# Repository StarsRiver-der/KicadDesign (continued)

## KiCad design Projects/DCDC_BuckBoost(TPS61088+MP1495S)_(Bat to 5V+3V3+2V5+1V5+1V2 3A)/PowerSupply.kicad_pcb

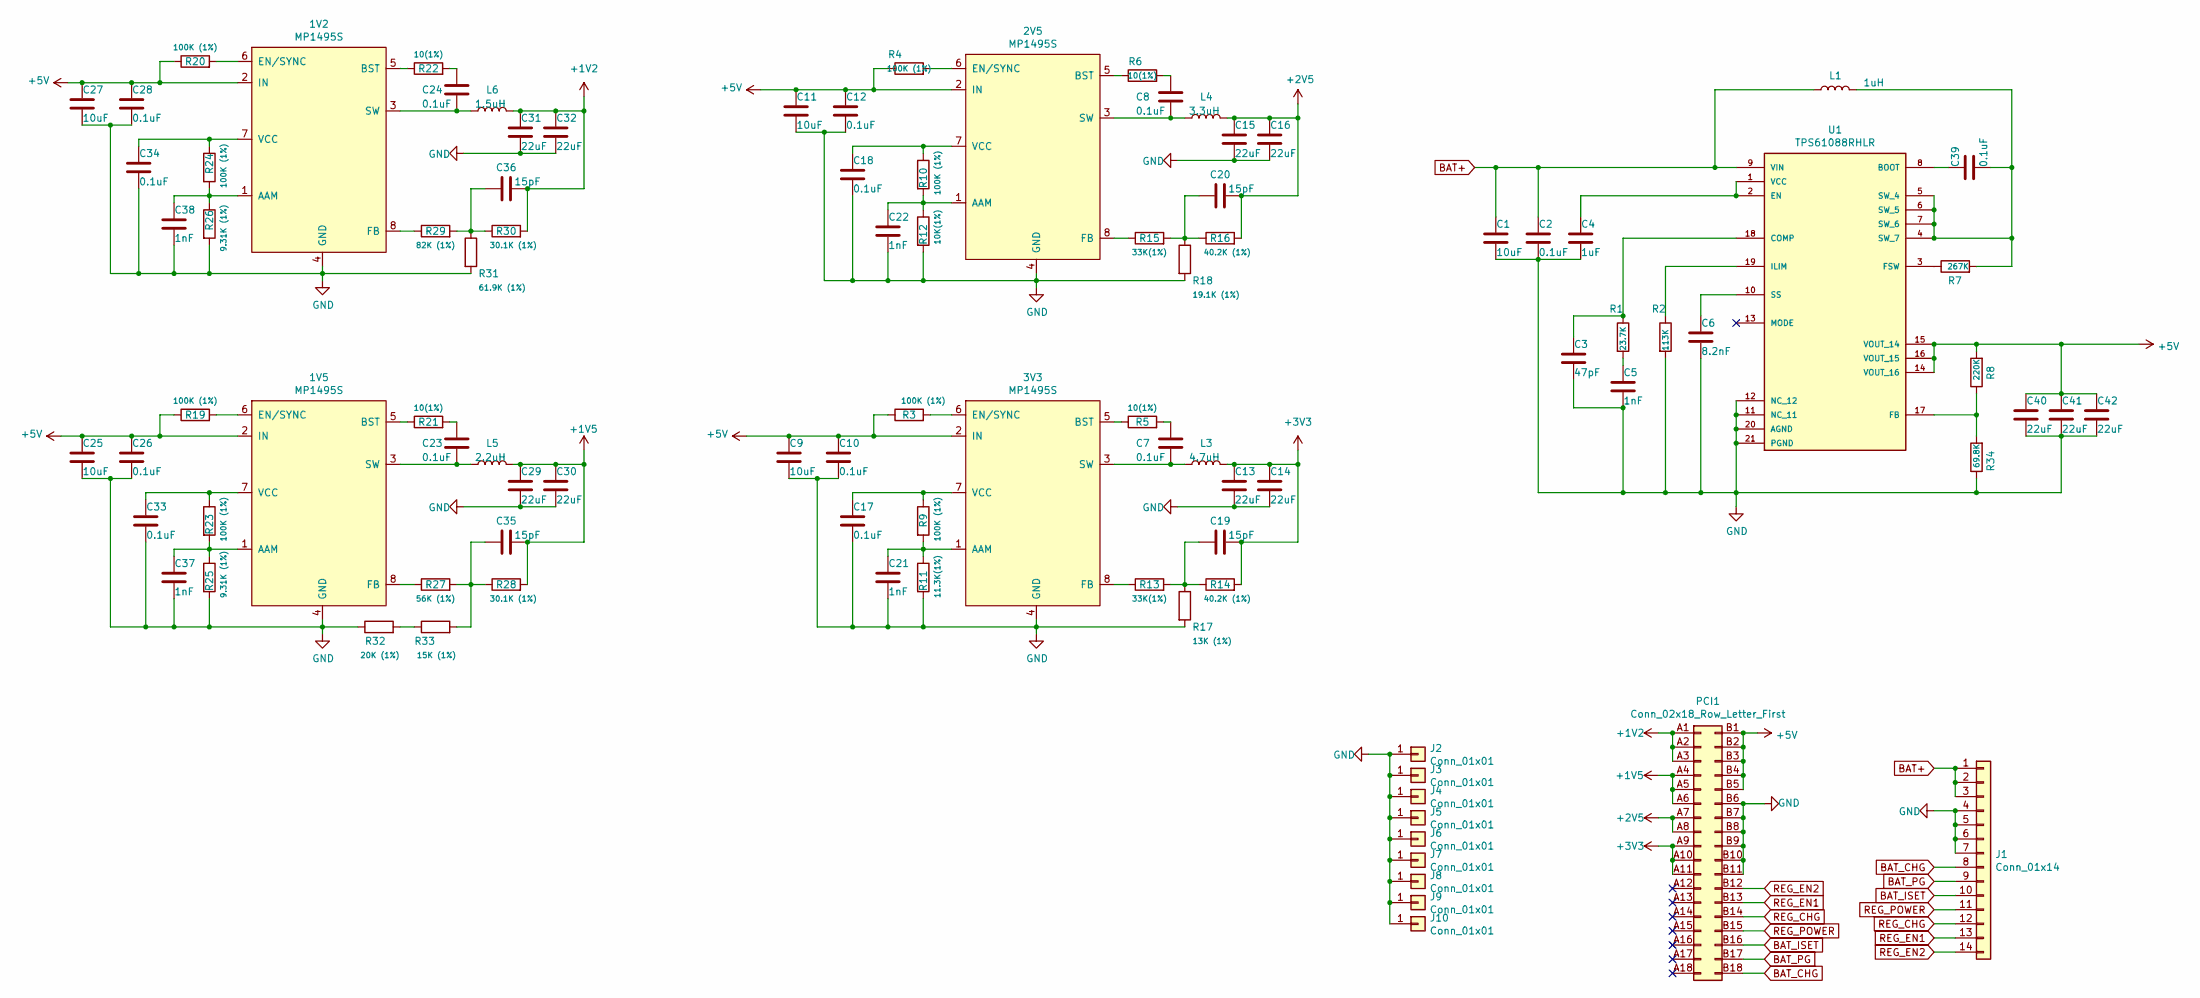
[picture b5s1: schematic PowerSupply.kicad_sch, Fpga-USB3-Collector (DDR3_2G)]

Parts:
1V2, 1V5, 2V5, 3V3: MP1495S; SOT65P280X100-8N
C1, C9, C11, C25, C27: 10uF; C_0603_1608Metric
C2, C7, C8, C10, C12, C17, C18, C23, C24, C26, C28, C33, C34, C39: 0.1uF; C_0402_1005Metric
C3: 47pF; C_0402_1005Metric
C4: 1uF; C_0402_1005Metric
C5, C21, C22, C37, C38: 1nF; C_0402_1005Metric
C6: 8.2nF; C_0402_1005Metric
C13, C14, C15, C16, C29, C30, C31, C32, C40, C41, C42: 22uF; C_0603_1608Metric
C19, C20, C35, C36: 15pF; C_0402_1005Metric
J1: Conn_01x14; Hirose_FH12-14S-0.5SH_1x14-1MP_P0.50mm_Horizontal
J2, J3, J4, J5, J6, J7, J8, J9, J10: Conn_01x01; pad-6-1.5
L1: 1uH; L_Sunlord_MWSA0518_5.4x5.2mm
L3: 4.7uH; L_Sunlord_MWSA0518_5.4x5.2mm
L4: 3.3uH; L_Sunlord_MWSA0518_5.4x5.2mm
L5: 2.2uH; L_Sunlord_MWSA0518_5.4x5.2mm
L6: 1.5uH; L_Sunlord_MWSA0518_5.4x5.2mm
PCI1: Conn_02x18_Row_Letter_First; BUS_PCIexpress_x1
R1: 23.7K; R_0402_1005Metric
R2: 113K; R_0402_1005Metric
R3, R4, R9, R10, R19, R20, R23, R24: 100K (1%); R_0402_1005Metric
R5, R6, R21, R22: 10(1%); R_0402_1005Metric
R7: 267K; R_0402_1005Metric
R8: 220K; R_0402_1005Metric
R11: 11.3K(1%); R_0402_1005Metric
R12: 10K(1%); R_0402_1005Metric
R13, R15: 33K(1%); R_0402_1005Metric
R14, R16: 40.2K (1%); R_0402_1005Metric
R17: 13K (1%); R_0402_1005Metric
R18: 19.1K (1%); R_0402_1005Metric
R25, R26: 9.31K (1%); R_0402_1005Metric
R27: 56K (1%); R_0402_1005Metric
R28, R30: 30.1K (1%); R_0402_1005Metric
R29: 82K (1%); R_0402_1005Metric
R31: 61.9K (1%); R_0402_1005Metric
R32: 20K (1%); R_0402_1005Metric
R33: 15K (1%); R_0402_1005Metric
R34: 69.8K; R_0402_1005Metric
U1: TPS61088RHLR; IC_TPS61088RHLR; PARTREV 4219071/A 05/2017

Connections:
+1V2: C31.1, C32.1, C36.2, L6.2, PCI1.A1, PCI1.A2, PCI1.A3, R30.2
+1V5: C29.1, C30.1, C35.2, L5.2, PCI1.A4, PCI1.A5, PCI1.A6, R28.2
+2V5: C15.1, C16.1, C20.2, L4.2, PCI1.A7, PCI1.A8, R16.2
+3V3: C13.1, C14.1, C19.2, L3.2, PCI1.A9, PCI1.A10, PCI1.A11, R14.2
+5V: 1V2.2 (IN), 1V5.2 (IN), 2V5.2 (IN), 3V3.2 (IN), C9.1, C10.1, C11.1, C12.1, C25.1, C26.1, C27.1, C28.1, C40.1, C41.1, C42.1, PCI1.B1, PCI1.B2, PCI1.B3, PCI1.B4, PCI1.B5, R3.1, R4.1, R8.2, R19.1, R20.1, U1.14 (VOUT_16), U1.15 (VOUT_14), U1.16 (VOUT_15)
BAT+: C1.1, C2.1, J1.1, J1.2, J1.3, L1.1, U1.9 (VIN)
BAT_CHG: J1.8, PCI1.B18
BAT_ISET: J1.10, PCI1.B16
BAT_PG: J1.9, PCI1.B17
GND: 1V2.4 (GND), 1V5.4 (GND), 2V5.4 (GND), 3V3.4 (GND), C1.2, C2.2, C3.2, C4.2, C5.2, C6.2, C9.2, C10.2, C11.2, C12.2, C13.2, C14.2, C15.2, C16.2, C17.2, C18.2, C21.2, C22.2, C25.2, C26.2, C27.2, C28.2, C29.2, C30.2, C31.2, C32.2, C33.2, C34.2, C37.2, C38.2, C40.2, C41.2, C42.2, J1.4, J1.5, J1.6, J1.7, J2.1, J3.1, J4.1, J5.1, J6.1, J7.1, J8.1, J9.1, J10.1, PCI1.B6, PCI1.B7, PCI1.B8, PCI1.B9, PCI1.B10, PCI1.B11, R2.2, R11.2, R12.2, R17.2, R18.2, R25.2, R26.2, R31.2, R32.1, R34.1, U1.11 (NC_11), U1.12 (NC_12), U1.20 (AGND), U1.21 (PGND)
unnamed: 1V2.1 (AAM), C38.1, R24.2, R26.1
unnamed: 1V2.3 (SW), C24.2, L6.1
unnamed: 1V2.5 (BST), R22.1
unnamed: 1V2.6 (EN/SYNC), R20.2
unnamed: 1V2.7 (VCC), C34.1, R24.1
unnamed: 1V2.8 (FB), R29.1
unnamed: 1V5.1 (AAM), C37.1, R23.2, R25.1
unnamed: 1V5.3 (SW), C23.2, L5.1
unnamed: 1V5.5 (BST), R21.1
unnamed: 1V5.6 (EN/SYNC), R19.2
unnamed: 1V5.7 (VCC), C33.1, R23.1
unnamed: 1V5.8 (FB), R27.1
unnamed: 2V5.1 (AAM), C22.1, R10.2, R12.1
unnamed: 2V5.3 (SW), C8.2, L4.1
unnamed: 2V5.5 (BST), R6.1
unnamed: 2V5.6 (EN/SYNC), R4.2
unnamed: 2V5.7 (VCC), C18.1, R10.1
unnamed: 2V5.8 (FB), R15.1
unnamed: 3V3.1 (AAM), C21.1, R9.2, R11.1
unnamed: 3V3.3 (SW), C7.2, L3.1
unnamed: 3V3.5 (BST), R5.1
unnamed: 3V3.6 (EN/SYNC), R3.2
unnamed: 3V3.7 (VCC), C17.1, R9.1
unnamed: 3V3.8 (FB), R13.1
unnamed: C3.1, R1.1, U1.18 (COMP)
unnamed: C4.1, U1.1 (VCC), U1.2 (EN)
unnamed: C5.1, R1.2
unnamed: C6.1, U1.10 (SS)
unnamed: C7.1, R5.2
unnamed: C8.1, R6.2
unnamed: C19.1, R13.2, R14.1, R17.1
unnamed: C20.1, R15.2, R16.1, R18.1
unnamed: C23.1, R21.2
unnamed: C24.1, R22.2
unnamed: C35.1, R27.2, R28.1, R33.2
unnamed: C36.1, R29.2, R30.1, R31.1
unnamed: C39.1, U1.8 (BOOT)
unnamed: C39.2, L1.2, R7.2, U1.4 (SW_7), U1.5 (SW_4), U1.6 (SW_5), U1.7 (SW_6)
unnamed: R2.1, U1.19 (ILIM)
unnamed: R7.1, U1.3 (FSW)
unnamed: R32.2, R33.1
unnamed: R8.1, R34.2, U1.17 (FB)
REG_CHG: J1.12, PCI1.B14
REG_EN1: J1.13, PCI1.B13
REG_EN2: J1.14, PCI1.B12
REG_POWER: J1.11, PCI1.B15

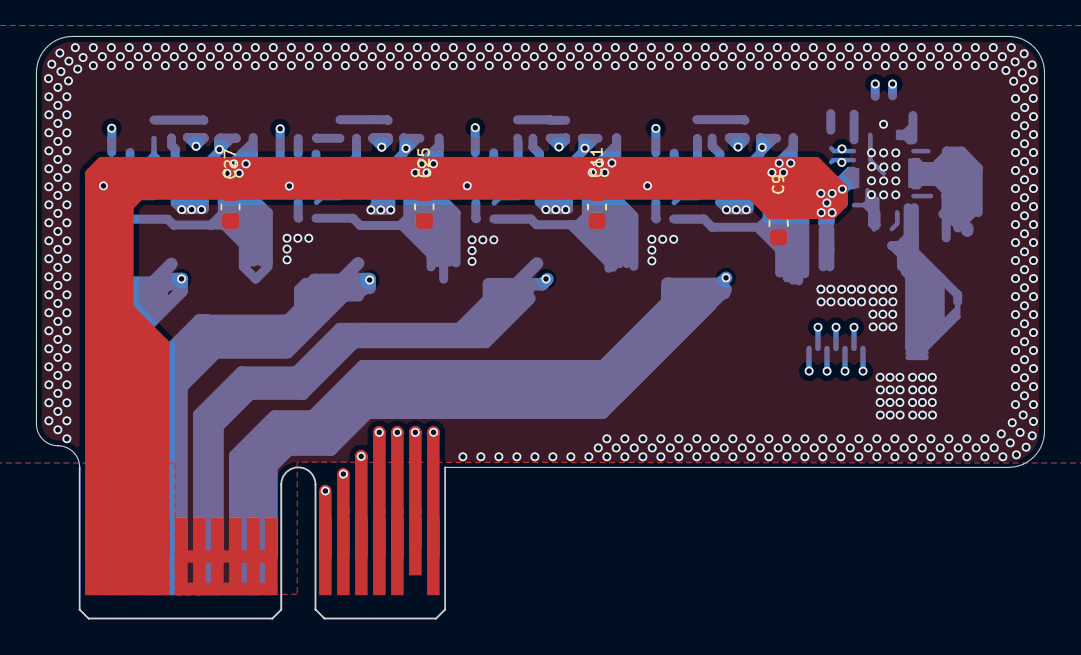
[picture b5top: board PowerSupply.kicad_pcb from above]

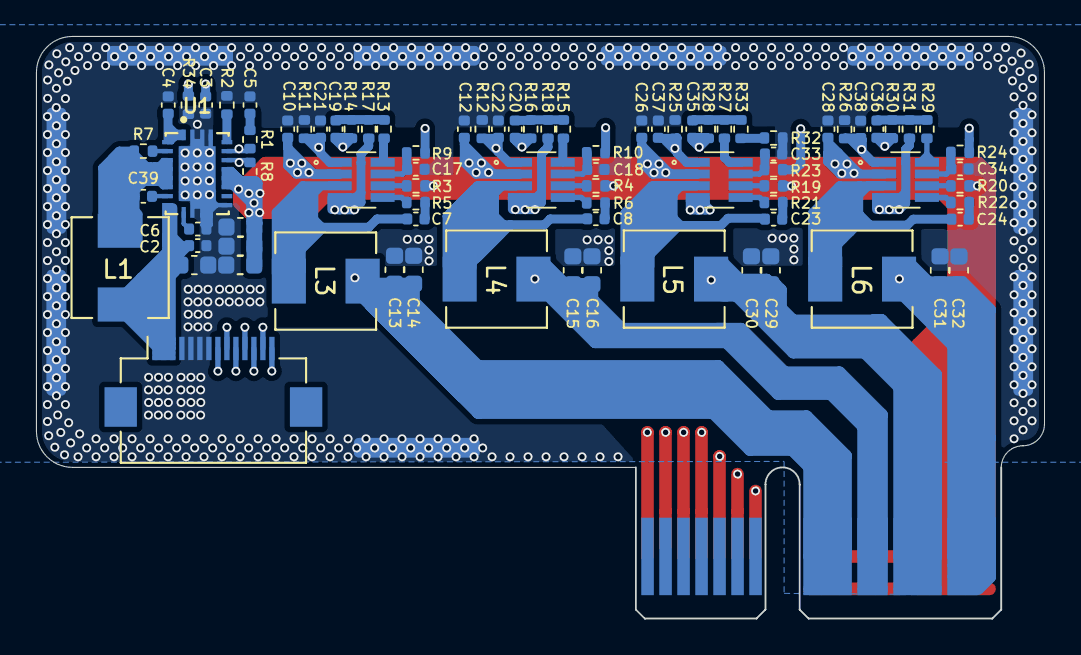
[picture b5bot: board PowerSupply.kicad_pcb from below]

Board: 4 copper layers, 56.0 x 32.3 mm, 97 parts (92 on the bottom side), 56 nets.
